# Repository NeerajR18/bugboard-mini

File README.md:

# bugboard-mini
Small Size development board based on the STM32G431KBT6

## Features
- Small PCB, 20 mm x 25 mm
- Debug headers included
- Supports USART

## PCB

#### Schematic

#### PCB

- PCB front

- PCB back

Made fully in KiCad.

## Bill of Materials

| MPN | Quantity | Unit Price (USD) | Ext. Price (USD) | Link |
|---|---:|---:|---:|---|
| STM32G431KBT6 | 1 | $7.03 | $7.03 | [LionCircuits](https://www.lioncircuits.com/parts/STM32G431KBT6) |
| RC0402FR-1010KL | 100 | $0.0037 | $0.37 | [Robu](https://robu.in/product/rc0402fr-1010kl-yageo-0-063w-thick-film-resistors-%c2%b1100ppm-%e2%84%83-%c2%b11-10k%cf%89-0402-chip-resistor-surface-mount-rohs/) |
| RC0402FR-075K1L | 100 | $0.002 | $0.20 | [Robu](https://robu.in/product/rc0402fr-075k1l-yageo-res-thick-film-0402-5-1k-ohm-1-0-063w1-16w-%c2%b1100ppm-c-pad-smd-t-r/) |
| XC6206P182MR | 5 | $0.037 | $0.185 | [Robu](https://robu.in/product/xc6206p182mr-twgmc-70db1khz-300ma-fixed-1-8v-positive-electrode-6v-sot-23-voltage-regulators-linear-low-drop-out-ldo-regulators-rohs/) |
| TCC0402X5R104K500AT | 100 | $0.0025 | $0.25 | [Robu](https://robu.in/product/tcc0402x5r104k500at-cctc-smt-ceramic-capacitors-0402-x5r-104k100nf%c2%b110-rated-voltage50v-thickness0-50mm-tape/) |
| PRTR5V0U2X | 5 | $0.095 | $0.475 | [Robu](https://robu.in/product/prtr5v0u2x215-nexperia-prtr5v0u2x215-esd-protection-device-tvs-7-5-v-sot-143b-4-pins-5-5-v-prtr5/) |
| TYPE-C-31-M-12 | 2 | $0.40 | $0.80 | [Robu](https://robu.in/product/type-c-31-m-12-hroparts-5a-1-16p-female-type-c-smd-usb-connectors-rohs/) |
| SMD0603P050TF | 5 | $0.13 | $0.65 | [Robu](https://robu.in/product/smd0603p050tf-pttcpolytronics-tech-6v-40a-500ma-1a-0603-resettable-rohs/) |
| TS-1088-AR02016 | 5 | $0.029 | $0.145 | [Robu](https://robu.in/product/1-month-warranty-470/) |
| CC0402MRX5R5BB106 | 10 | $0.048 | $0.48 | [Robu](https://robu.in/product/cc0402mrx5r5bb106-yageo-cap-smd-mlcc-10-%c2%b5f-6-3-v-0402-1005-metric-20-x5r-cc-series/) |
| PCB from ROBU | 5 | $1.90 | $9.52 | [Robu](https://robu.in/product/online-pcb-manufacturing-service/) |
| Shipping Charges | - | $5.00 | $5.00 | - |
| **Total** | | **$14.6772** | | |

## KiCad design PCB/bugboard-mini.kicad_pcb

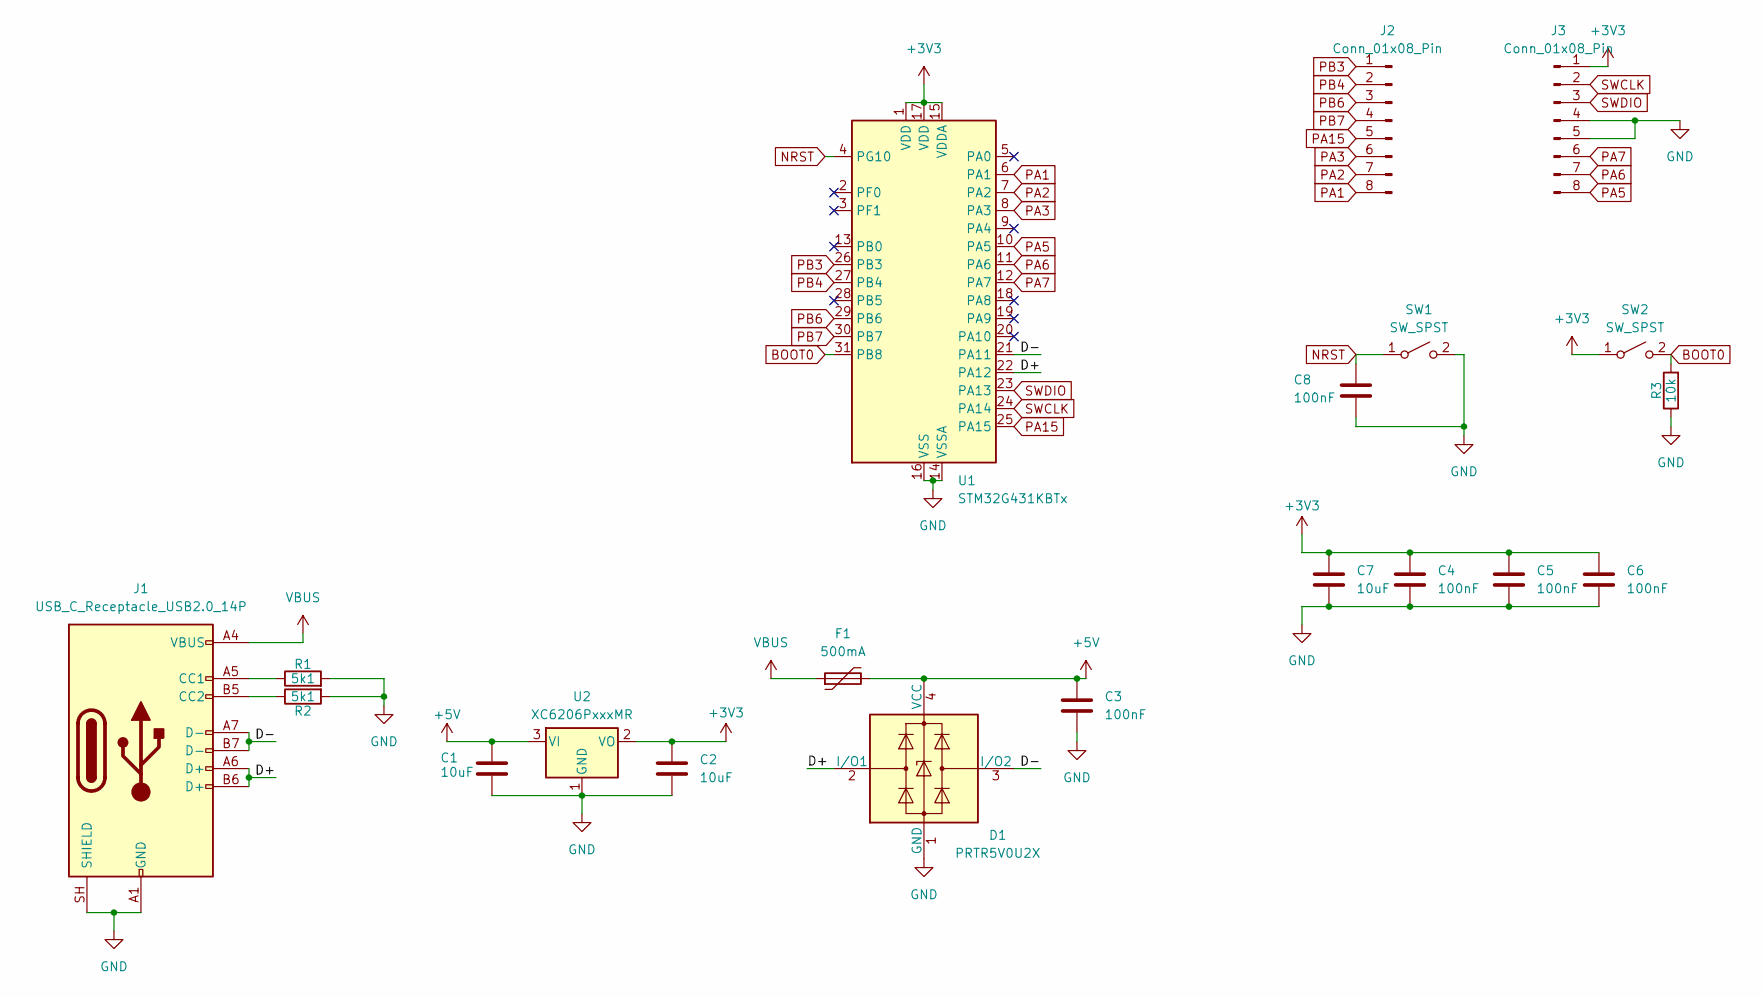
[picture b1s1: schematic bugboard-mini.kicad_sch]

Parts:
C1, C2, C7: 10uF; C_0402_1005Metric
C3, C4, C5, C6, C8: 100nF; C_0402_1005Metric
D1: PRTR5V0U2X; SOT-143
F1: 500mA; Fuse_0603_1608Metric
J1: USB_C_Receptacle_USB2.0_14P; USB_C_Receptacle_HRO_TYPE-C-31-M-12
J2, J3: Conn_01x08_Pin; PinHeader_1x08_P2.54mm_Vertical
R1, R2: 5k1; C_0402_1005Metric
R3: 10k; C_0402_1005Metric
SW1, SW2: SW_SPST; SW_SPST_TS-1088-xR020
U1: STM32G431KBTx; LQFP-32_7x7mm_P0.8mm
U2: XC6206PxxxMR; SOT-23-3

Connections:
+3V3: C2.1, C4.1, C5.1, C6.1, C7.1, J3.1, SW2.1 (A), U1.1 (VDD), U1.15 (VDDA), U1.17 (VDD), U2.2 (VO)
+5V: C1.1, C3.1, D1.4 (VCC), F1.2, U2.3 (VI)
/D+: D1.2 (I/O1), J1.A6 (D+), J1.B6 (D+), U1.22 (PA12)
/D-: D1.3 (I/O2), J1.A7 (D-), J1.B7 (D-), U1.21 (PA11)
BOOT0: R3.2, SW2.2 (B), U1.31 (PB8)
GND: C1.2, C2.2, C3.2, C4.2, C5.2, C6.2, C7.2, C8.2, D1.1 (GND), J1.A1 (GND), J1.A12 (GND), J1.B1 (GND), J1.B12 (GND), J1.SH (SHIELD), J3.4, J3.5, R1.2, R2.2, R3.1, SW1.2 (B), U1.14 (VSSA), U1.16 (VSS), U1.32 (VSS), U2.1 (GND)
NRST: C8.1, SW1.1 (A), U1.4 (PG10)
unnamed: J1.A5 (CC1), R1.1
unnamed: J1.B5 (CC2), R2.1
PA1: J2.8, U1.6 (PA1)
PA2: J2.7, U1.7 (PA2)
PA3: J2.6, U1.8 (PA3)
PA5: J3.8, U1.10 (PA5)
PA6: J3.7, U1.11 (PA6)
PA7: J3.6, U1.12 (PA7)
PA15: J2.5, U1.25 (PA15)
PB3: J2.1, U1.26 (PB3)
PB4: J2.2, U1.27 (PB4)
PB6: J2.3, U1.29 (PB6)
PB7: J2.4, U1.30 (PB7)
SWCLK: J3.2, U1.24 (PA14)
SWDIO: J3.3, U1.23 (PA13)
VBUS: F1.1, J1.A4 (VBUS), J1.A9 (VBUS), J1.B4 (VBUS), J1.B9 (VBUS)

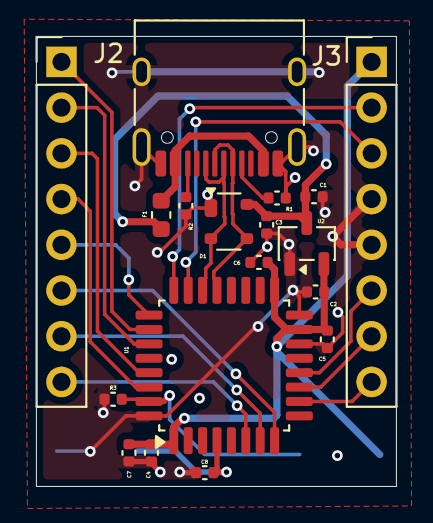
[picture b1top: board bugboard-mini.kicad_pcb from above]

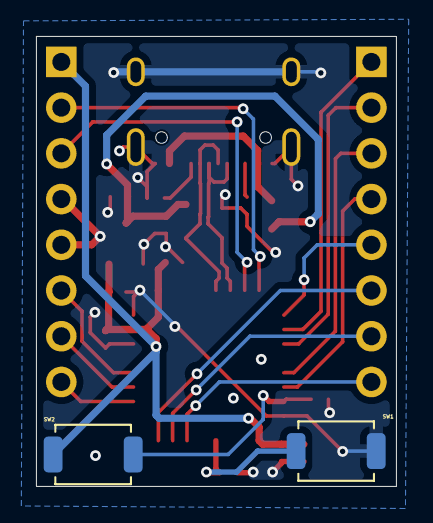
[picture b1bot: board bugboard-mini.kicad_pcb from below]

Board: 2 copper layers, 20.0 x 25.0 mm, 20 parts (2 on the bottom side), 23 nets.
